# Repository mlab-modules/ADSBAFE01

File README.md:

# ADSBAFE01 - 1090 MHz ADS-B analog front-end

ADSBAFE01 is a complete 1090 MHz analog front-end for ADS-B / Mode-S reception. The module integrates RF filtering, low-noise amplification, logarithmic power detection and high-speed pulse shaping. It is intended to deliver a logic pulse stream corresponding to the RF envelope together with auxiliary RSSI information for sensitivity control and signal quality evaluation.

## Intended use

ADSBAFE01 is designed as an analog front-end for custom ADS-B receivers where digital demodulation and message decoding are implemented externally (MCU, FPGA, SDR backend, etc.). The module does not perform protocol decoding; it delivers time-accurate envelope pulses and auxiliary RSSI information for higher-layer processing.

## Functional overview

The RF signal enters through a 50 Ω MCX connector and immediately passes a 1090 MHz SAW band-pass filter (~30 MHz bandwidth). This suppresses strong out-of-band signals before amplification. The filtered signal is amplified by a BGA2818 LNA with approximately +30 dB gain. Then logarithmic power detector (AD8313) converts the RF envelope into a baseband voltage proportional to signal level. This node is intentionally kept lightly loaded because additional capacitance directly degrades slew rate and therefore timing accuracy of the detected pulses (see schematic notes ).

The detector output is processed in two parallel paths:

1. A high-speed comparator path generating digital pulses.
2. A peak-detection and sample-and-hold path providing RSSI information.

This separation allows reliable time-domain decoding while still exposing signal strength information for adaptive thresholding or diagnostics.

### Pulse extraction path

The comparator (MCP6566) converts the detector voltage into a CMOS pulse stream. Its propagation delay is on the order of 50 ns with ~20 ns fall time, which is sufficient for 1 µs ADS-B pulses.

The detection threshold is not fixed. It is derived from bias networks controlled by a 100 kΩ digital potentiometer (MCP4017, I²C). This allows software-controlled sensitivity adjustment without hardware modification. Low-frequency RC filtering in the bias network (fc ≈ 159 Hz) stabilizes the reference and suppresses slow variations.

The resulting `PULSES` output can be directly connected to:

* MCU timer capture input
* FPGA input
* Fast interrupt-capable GPIO

### RSSI and peak detection

For signal strength evaluation, the module implements an active peak detector (op-amp based). During a decode window, the peak value of the (inverted) log-detector output is sampled and held. The reset discharge time constant is approximately 44 ns, with ~95 % discharge in ~132 ns, enabling packet-level RSSI measurements without excessive memory between adjacent pulses.

The analog RSSI signal can be read by an external ADC if quantitative signal strength estimation is required.

### Electrical parameters

| Parameter          | Value / Description       |
| ------------------ | ------------------------- |
| Supply voltage     | 3.3 V                     |
| RF frequency       | 1090 MHz (ADS-B / Mode-S) |
| RF input impedance | 50 Ω                      |
| LNA gain           | ~+30 dB                   |
| Comparator delay   | ~50 ns                    |
| Logic levels       | 3.3 V CMOS                |
| Threshold control  | I²C digital potentiometer |

The module includes input decoupling (10 µF + 100 nF) and supply protection (TVS diode) as shown in the schematic .

### Connectors

#### RF input (J3)

Type: MCX with impedance: 50 Ω

#### IO header (J1, 2×12)

The IO header exposes digital control, RSSI and interface signals. Series resistors provide basic IO protection and edge damping.

| Signal      | Direction       | Description                         |
| ----------- | --------------- | ----------------------------------- |
| PULSES      | Output          | Digital ADS-B envelope pulses       |
| RF_LEVEL    | Output (analog) | Log-detector RSSI voltage           |
| DECODE      | Input           | Enables RSSI peak sampling          |
| RSSI_HOLD   | Input           | Controls sample/hold state          |
| RSSI_DSCHRG | Input           | Forces RSSI capacitor discharge     |
| MTL_HI_PWM  | Input           | Comparator reference control (high) |
| MTL_LO_PWM  | Input           | Comparator reference control (low)  |
| MTL_HI_BIAS | Internal / test | Bias node (high threshold)          |
| MTL_LO_BIAS | Internal / test | Bias node (low threshold)           |
| I2C1_SCL    | Input           | I²C clock (digital potentiometer)   |
| I2C1_SDA    | Bidirectional   | I²C data                            |
| +3V3        | —               | Supply                              |
| GND         | —               | Ground                              |

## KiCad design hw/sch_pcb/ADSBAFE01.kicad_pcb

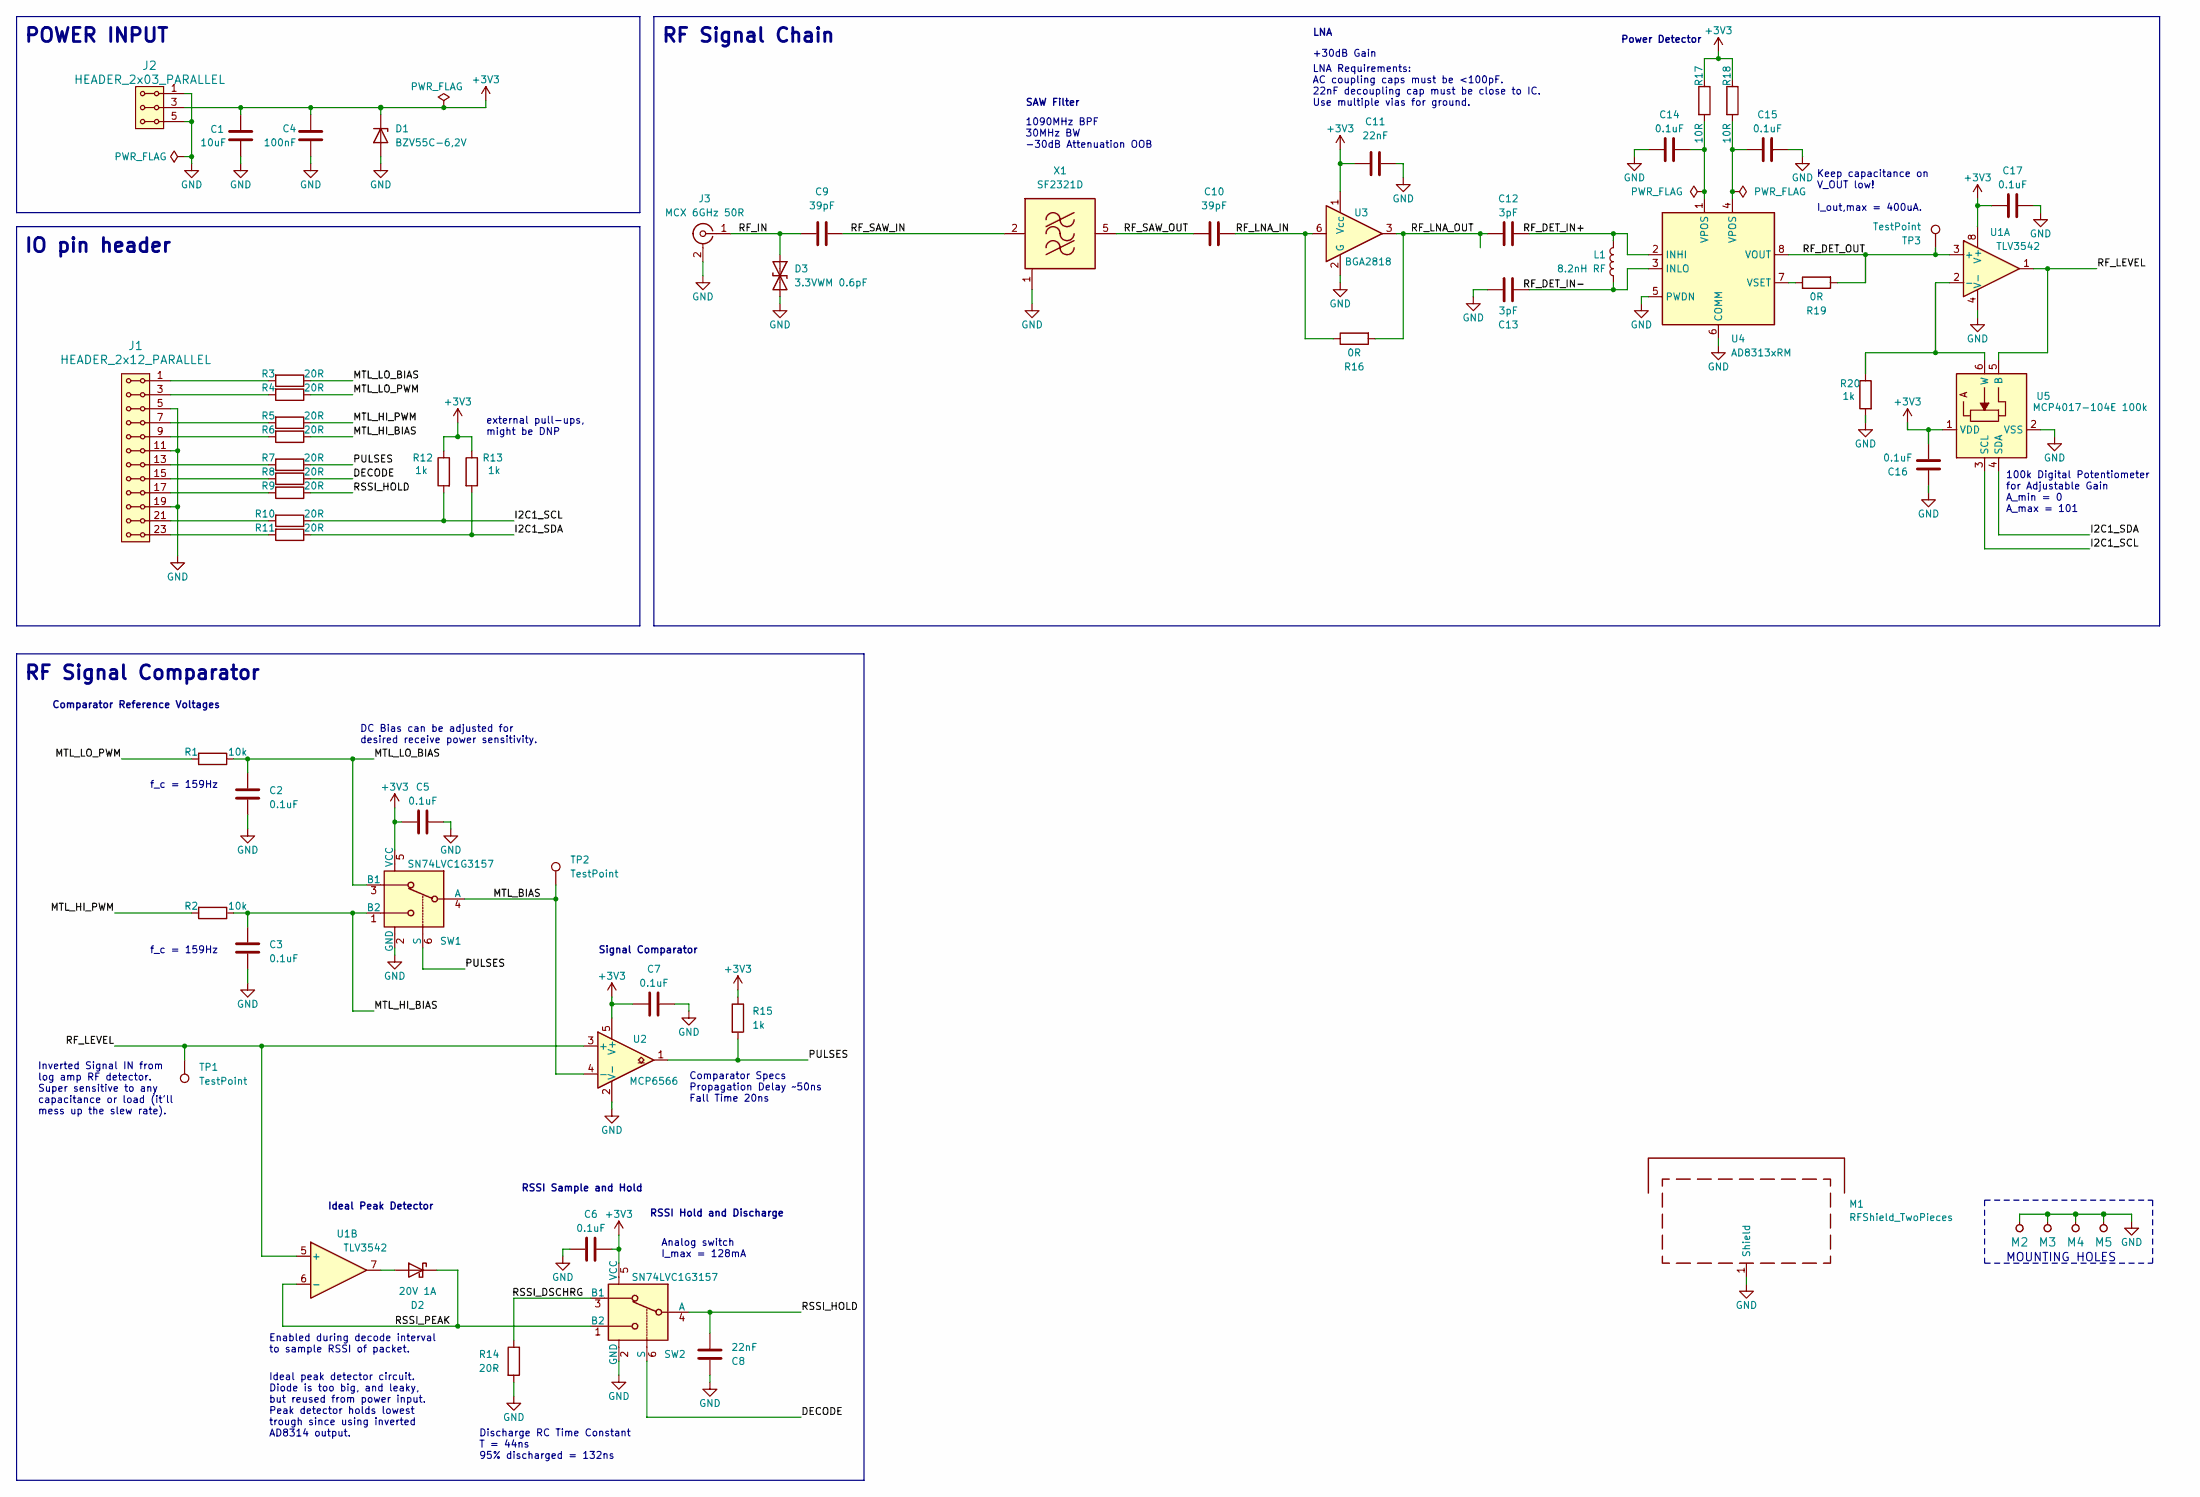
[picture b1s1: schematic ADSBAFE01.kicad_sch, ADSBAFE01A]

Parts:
C1: 10uF; C_0805_2012Metric_Pad1.18x1.45mm_HandSolder
C2, C3, C5, C6, C7, C14, C15, C16, C17: 0.1uF; C_0603_1608Metric_Pad1.08x0.95mm_HandSolder; MPN CC0402KRX7R7BB104
C4: 100nF; C_0805_2012Metric_Pad1.18x1.45mm_HandSolder
C8, C11: 22nF; C_0603_1608Metric_Pad1.08x0.95mm_HandSolder; MPN CC0402KRX7R9BB223
C9, C10: 39pF; C_0603_1608Metric_Pad1.08x0.95mm_HandSolder; MPN CC0402JRNPO9BN390
C12, C13: 3pF; C_0603_1608Metric_Pad1.08x0.95mm_HandSolder; MPN CQ0402CRNPO9BN3R0
D1: BZV55C-6,2V; D_MiniMELF
D2: 20V 1A; D_SOD-123; MPN PMEG2010ER,115
D3: 3.3VWM 0.6pF; D_SOD-523; MPN ESD7351XV2T1G
J1: HEADER_2x12_PARALLEL; Straight_2x12
J2: HEADER_2x03_PARALLEL; Straight_2x03
J3: MCX 6GHz 50R; MCX; MPN U.FL-R-SMT-1(80)
L1: 8.2nH RF; L_0402_1005Metric; MPN 0402HP-8N2XJRW
M1: RFShield_TwoPieces; Laird_Technologies_BMI-S-204-F_32.00x32.00mm
M2, M3, M4, M5: HOLE; MountingHole_3mm
R1, R2: 10k; R_0603_1608Metric_Pad0.98x0.95mm_HandSolder; MPN RC0402FR-0710KL
R3, R4, R5, R6, R7, R8, R9, R10, R11: 20R; R_0603_1608Metric_Pad0.98x0.95mm_HandSolder; MPN RC0402FR-0710KL
R12, R13, R15, R20: 1k; R_0603_1608Metric_Pad0.98x0.95mm_HandSolder; MPN RC0402FR-071KL
R14: 20R; R_0603_1608Metric_Pad0.98x0.95mm_HandSolder; MPN RC0402FR-0720RL
R16, R19: 0R; R_0603_1608Metric_Pad0.98x0.95mm_HandSolder; MPN RC0402JR-070RL
R17, R18: 10R; R_0603_1608Metric_Pad0.98x0.95mm_HandSolder; MPN RC0402FR-0710RL
SW1, SW2: SN74LVC1G3157; SOT-363_SC-70-6; MPN SN74LVC1G3157DCKR
TP1, TP2, TP3: TestPoint; TestPoint_Pad_D1.0mm
U1: TLV3542; VSSOP-8_3x3mm_P0.65mm; MPN TLV3542IDGKR
U2: MCP6566; SOT-353_SC-70-5; MPN MCP6566T-E/LT
U3: BGA2818; SOT-363_SC-70-6; MPN BGA2818,115
U4: AD8313xRM; MSOP-8_3x3mm_P0.65mm; MPN AD8313ARMZ
U5: MCP4017-104E 100k; SOT-363_SC-70-6; MPN MCP4017T-104E/LT
X1: SF2321D; Filter_SAW-6_3.8x3.8mm; MPN SF2321D

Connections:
+3V3: C1.1, C4.1, C5.1, C6.2, C7.1, C11.1, C16.2, C17.1, D1.1 (K), J2.3, J2.4, R12.1, R13.1, R15.1, R17.1, R18.1, SW1.5 (VCC), SW2.5 (VCC), U1.8 (V+), U2.5 (V+), U3.1 (Vcc), U5.1 (VDD)
/DECODE: R8.1, SW2.6 (S)
/I2C1_SCL: R10.1, R12.2, U5.3 (SCL)
/I2C1_SDA: R11.1, R13.2, U5.4 (SDA)
/MTL_BIAS: SW1.4 (A), TP2.1, U2.4 (-)
/MTL_HI_BIAS: C3.1, R2.1, R6.1, SW1.1 (B2)
/MTL_HI_PWM: R2.2, R5.1
/MTL_LO_BIAS: C2.1, R1.1, R3.1, SW1.3 (B1)
/MTL_LO_PWM: R1.2, R4.1
/PULSES: R7.1, R15.2, SW1.6 (S), U2.1
/RF_DET_IN+: C12.2, L1.1, U4.2 (INHI)
/RF_DET_IN-: C13.2, L1.2, U4.3 (INLO)
/RF_DET_OUT: R19.2, TP3.1, U1.3 (+), U4.8 (VOUT)
/RF_IN: C9.1, D3.1 (A1), J3.1 (In)
/RF_LEVEL: TP1.1, U1.1, U1.5 (+), U2.3 (+), U5.5 (B)
/RF_LNA_IN: C10.2, R16.1, U3.6
/RF_LNA_OUT: C12.1, R16.2, U3.3
/RF_SAW_IN: C9.2, X1.2 (IN)
/RF_SAW_OUT: C10.1, X1.5 (OUT)
/RSSI_DSCHRG: R14.1, SW2.3 (B1)
/RSSI_HOLD: C8.2, R9.1, SW2.4 (A)
/RSSI_PEAK: D2.1 (K), SW2.1 (B2), U1.6 (-)
GND: C1.2, C2.2, C3.2, C4.2, C5.2, C6.1, C7.2, C8.1, C11.2, C13.1, C14.1, C15.2, C16.1, C17.2, D1.2 (A), D3.2 (A2), J1.5, J1.6, J1.11, J1.12, J1.19, J1.20, J2.1, J2.2, J2.5, J2.6, J3.2 (Ext), M1.1 (Shield), M2.1, M3.1, M4.1, M5.1, R14.2, R20.2, SW1.2 (GND), SW2.2 (GND), U1.4 (V-), U2.2 (V-), U3.2 (G), U3.4 (G), U3.5 (G), U4.5 (PWDN), U4.6 (COMM), U5.2 (VSS), X1.1 (GND), X1.3 (GND), X1.4 (GND), X1.6 (GND)
unnamed: C14.2, R17.2, U4.1 (VPOS)
unnamed: C15.1, R18.2, U4.4 (VPOS)
unnamed: D2.2 (A), U1.7
unnamed: J1.1, J1.2, R3.2
unnamed: J1.3, J1.4, R4.2
unnamed: J1.7, J1.8, R5.2
unnamed: J1.9, J1.10, R6.2
unnamed: J1.13, J1.14, R7.2
unnamed: J1.15, J1.16, R8.2
unnamed: J1.17, J1.18, R9.2
unnamed: J1.21, J1.22, R10.2
unnamed: J1.23, J1.24, R11.2
unnamed: R20.1, U1.2 (-), U5.6 (W)
unnamed: R19.1, U4.7 (VSET)

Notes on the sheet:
LNA
Comparator Reference Voltages
1090MHz BPF 30MHz BW -30dB Attenuation OOB
Keep capacitance on V_OUT low! I_out,max = 400uA.
100k Digital Potentiometer for Adjustable Gain A_min = 0 A_max = 101
Ideal Peak Detector
f_c = 159Hz
Analog switch I_max = 128mA
Enabled during decode interval to sample RSSI of packet.
RF Signal Comparator
SAW Filter
MOUNTING HOLES
RF Signal Chain
+30dB Gain
Signal Comparator
f_c = 159Hz
Comparator Specs Propagation Delay ~50ns Fall Time 20ns
RSSI Sample and Hold
DC Bias can be adjusted for desired receive power sensitivity.
LNA Requirements: AC coupling caps must be <100pF. 22nF decoupling cap must be close to IC. Use multiple vias for ground.
RSSI Hold and Discharge
IO pin header
external pull-ups, might be DNP
Ideal peak detector circuit. Diode is too big, and leaky, but reused from power input. Peak detector holds lowest trough since using inverted AD8314 output.
POWER INPUT
Power Detector
Discharge RC Time Constant T = 44ns 95% discharged = 132ns
Inverted Signal IN from log amp RF detector. Super sensitive to any capacitance or load (it'll mess up the slew rate).

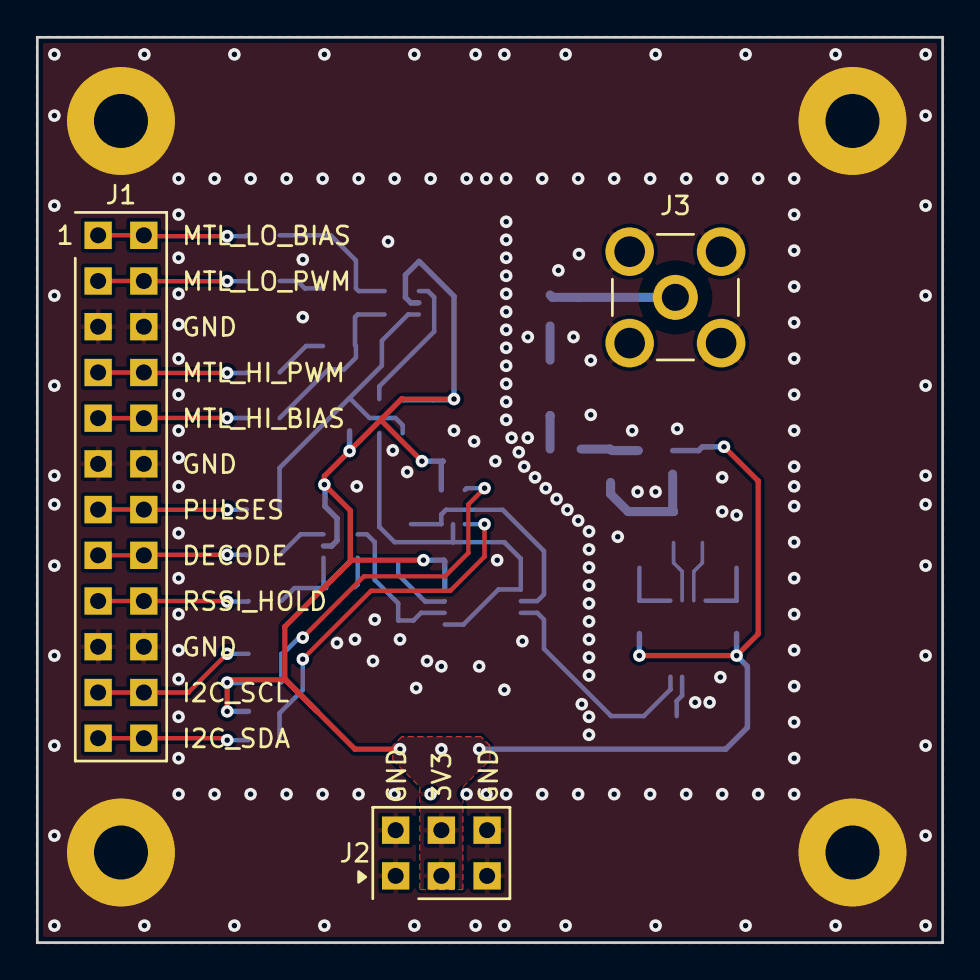
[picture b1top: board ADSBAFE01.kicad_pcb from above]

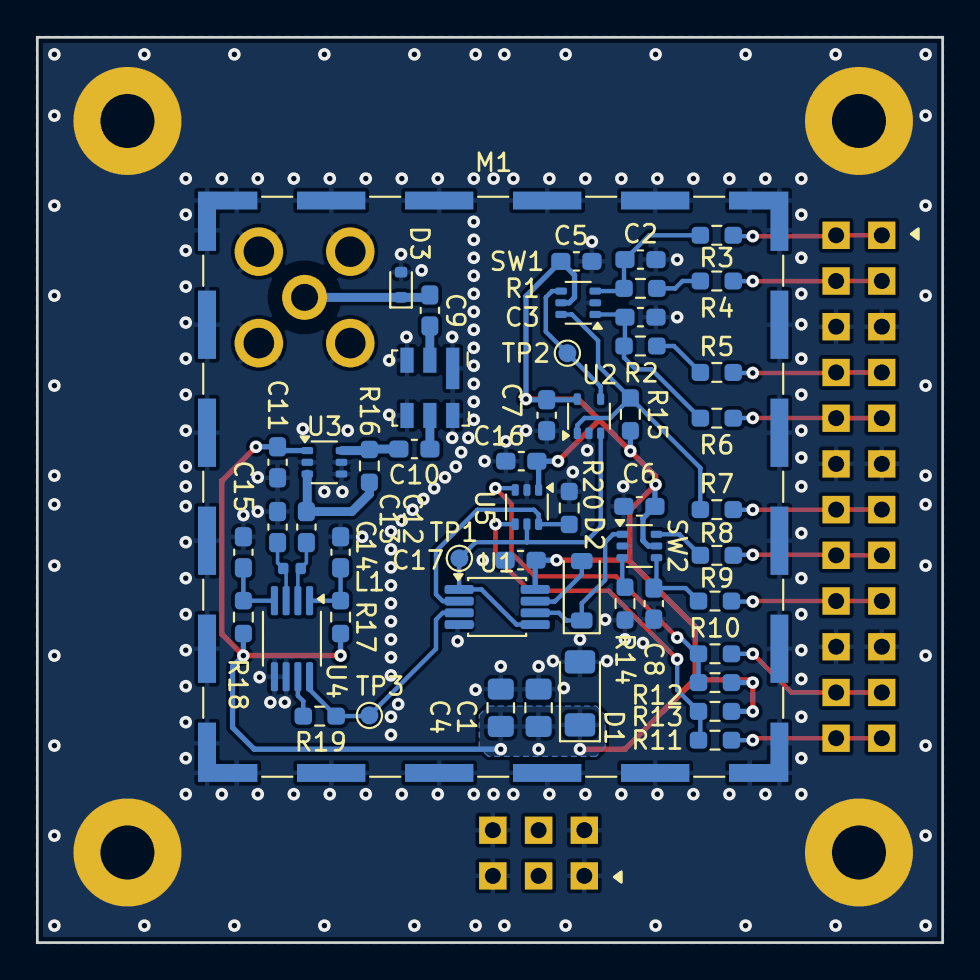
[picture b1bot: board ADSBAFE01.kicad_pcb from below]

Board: 2 copper layers, 50.3 x 50.3 mm, 60 parts (53 on the bottom side), 37 nets.

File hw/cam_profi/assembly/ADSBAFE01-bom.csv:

Component,Description,Part,References,Value,Footprint,Quantity Per PCB,Datasheet,mpn,ust_id
1,Unpolarized capacitor,C,C12C13,3pF,C_0603_1608Metric_Pad1.08x0.95mm_HandSolder,2,~,CQ0402CRNPO9BN3R0,
2,Unpolarized capacitor,C,C9C10,39pF,C_0603_1608Metric_Pad1.08x0.95mm_HandSolder,2,~,CC0402JRNPO9BN390,
3,Unpolarized capacitor,C,C8C11,22nF,C_0603_1608Metric_Pad1.08x0.95mm_HandSolder,2,~,CC0402KRX7R9BB223,
4,Unpolarized capacitor,C,C2C3C5C6C7C14C15C16C17,0.1uF,C_0603_1608Metric_Pad1.08x0.95mm_HandSolder,9,~,CC0402KRX7R7BB104,
5,Unpolarized capacitor,C,C4,100nF,C_0805_2012Metric_Pad1.18x1.45mm_HandSolder,1,~,,5c70984712875079b91f8b4c
6,Unpolarized capacitor,C,C1,10uF,C_0805_2012Metric_Pad1.18x1.45mm_HandSolder,1,~,,5c70984812875079b91f8bbe
7,Schottky diode,D_Schottky,D2,20V 1A,D_SOD-123,1,~,"PMEG2010ER,115",
8,Bidirectional transient-voltage-suppression diode,D_TVS,D3,3.3VWM 0.6pF,D_SOD-523,1,https://www.onsemi.com/pdf/datasheet/esd7351-d.pdf,ESD7351XV2T1G,
9,Zener diode,D_Zener,D1,"BZV55C-6,2V",D_MiniMELF,1,~,,604b0326128750769e5b0f93
10,"2x03 2.54 mm pitch header, 2 pins next to each other are connected",HEADER_2x03_PARALLEL,J2,HEADER_2x03_PARALLEL,Straight_2x03,1,,,
11,"2x12 2.54 mm pitch header, 2 pins next to each other are connected",HEADER_2x12_PARALLEL,J1,HEADER_2x12_PARALLEL,Straight_2x12,1,,,
12,"coaxial connector (BNC, SMA, SMB, SMC, Cinch/RCA, LEMO, ...)",Conn_Coaxial,J3,MCX 6GHz 50R,MCX,1,~,U.FL-R-SMT-1(80),
13,Inductor,L,L1,8.2nH RF,L_0402_1005Metric,1,~,0402HP-8N2XJRW,
14,Two-piece EMI RF shielding cabinet,RFShield_TwoPieces,M1,RFShield_TwoPieces,Laird_Technologies_BMI-S-204-F_32.00x32.00mm,1,~,,5c72751c1287500b4e11301a
15,Resistor,R,R16R19,0R,R_0603_1608Metric_Pad0.98x0.95mm_HandSolder,2,~,RC0402JR-070RL,
16,Resistor,R,R17R18,10R,R_0603_1608Metric_Pad0.98x0.95mm_HandSolder,2,~,RC0402FR-0710RL,
17,Resistor,R,R3R4R5R6R7R8R9R10R11R14,20R,R_0603_1608Metric_Pad0.98x0.95mm_HandSolder,10,~,RC0402FR-0710KL RC0402FR-0720RL,
18,Resistor,R,R12R13R15R20,1k,R_0603_1608Metric_Pad0.98x0.95mm_HandSolder,4,~,RC0402FR-071KL,
19,Resistor,R,R1R2,10k,R_0603_1608Metric_Pad0.98x0.95mm_HandSolder,2,~,RC0402FR-0710KL,
20,,SN74LVC1G3157,SW1SW2,SN74LVC1G3157,SOT-363_SC-70-6,2,https://www.ti.com/lit/ds/symlink/sn74lvc1g3157.pdf,SN74LVC1G3157DCKR,
21,"100 MHz to 2.5 GHz, 80 dB Logarithmic Detector / Controller, MSOP-8",AD8313xRM,U4,AD8313xRM,MSOP-8_3x3mm_P0.65mm,1,https://www.analog.com/media/en/technical-documentation/data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,AD8313ARMZ,
22,"MMIC wideband amplifier, DC-2.2GHz, +30dB @ 2150MHz, 3.3V, SOT-363",BGA2818,U3,BGA2818,SOT-363_SC-70-6,1,https://www.nxp.com/docs/en/data-sheet/BGA2818.pdf,"BGA2818,115",
23,"Low-Cost 128-Step Volatile I2C Digital Potentiometer, SC-70-6",MCP4017-xxxxLT,U5,MCP4017-104E 100k,SOT-363_SC-70-6,1,http://ww1.microchip.com/downloads/en/DeviceDoc/22147a.pdf,MCP4017T-104E/LT,
24,"Single 1.8V Low-Power Open-Drain Output Comparator, SOT-23-5/SC-70",MCP6566,U2,MCP6566,SOT-353_SC-70-5,1,http://ww1.microchip.com/downloads/en/DeviceDoc/MCP6566-6R-6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,MCP6566T-E/LT,
25,"200-MHz, Rail-to-Rail I/O, VSSOP-8",TLV3542,U1,TLV3542,VSSOP-8_3x3mm_P0.65mm_small,1,https://www.ti.com/lit/ds/symlink/tlv3542.pdf,TLV3542IDGKR,
26,,SAW-6_Filter,X1,SF2321D,Filter_SAW-6_3.8x3.8mm,1,https://www.mouser.com/datasheet/2/1100/sf2321d-1917641.pdf,SF2321D,

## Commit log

2026-02-16 Update metadata files
2026-02-18 first draft of layout
    Parts placement viable. Traces sketched only to test whether connections
    are viable.
2026-02-20 Layout done, silk WIP
2026-02-20 changed footprint U3, silk started
    Footprint of U3 changed to edited version which suits clearence 0,2mm.
2026-02-21 silk done
2026-02-21 reannotated, added 3d model of SAW
2026-02-21 symbols properties cleanup, final checks OK
2026-02-22 added via stitching
2026-02-22 Update workflows to KiCADv9.
2026-02-22 Update workflow files
2026-02-22 Automatic update of KiCAD outputs
2026-02-22 Layout improvements.
2026-02-22 Replace readme.
2026-03-03 Move footprints to standard MLAB libraries.
